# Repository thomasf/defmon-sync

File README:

defMon Sync Adapter is an adapter for the Commodore 64 computer. It is used to synchronize a tracker called defMon with other music equipment. It connects to the user port and outputs the following signals:
-LSDJ sync signal.
-nanoloop sync signal.
-midi clock.
-din sync.
-clock signal with adjustable resolution from 24ppqn to 2ppqn for Korg Volcas, TE Pocket Operators, Arturia Microbrute, MI Anushri etc.
It can only work as the master.
It should also work with Prophet64.

Original developer: Krzysztof Iwanowski

The firmware, PCB layouts and schematics are released under a Creative Commons cc-by-sa 3.0 license.

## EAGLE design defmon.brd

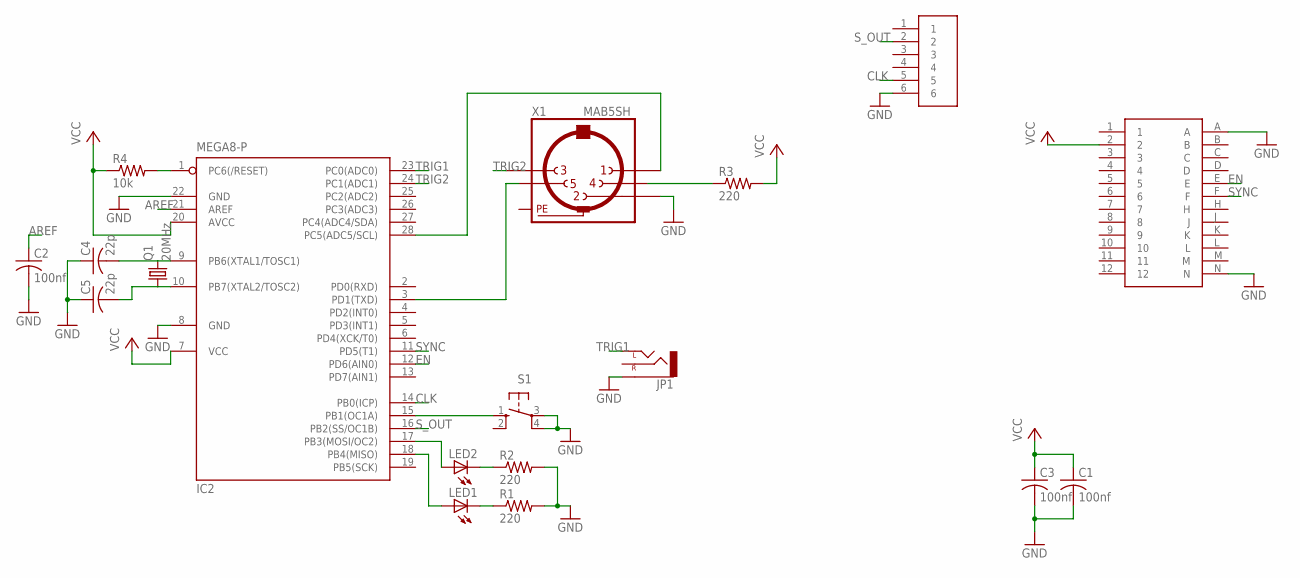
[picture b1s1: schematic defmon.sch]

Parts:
C1, C2, C3: 100nf; C025-025X050
C4, C5: 22p; C025-025X050
IC2: MEGA8-P; DIL28-3
JP1: AUDIO-JACKPTH; AUDIO-JACK
LED1, LED2: LED3MM
Q1: 20MHz; HC49U-V
R1, R2, R3: 220; 0204/7
R4: 10k; 0204/7
S1: 40-XX; B3F-40XX
U$1: GB
U$2: C64U
X1: MAB5SH

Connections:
AREF: C2.1, IC2.21 (AREF)
CLK: IC2.14 (PB0(ICP)), U$1.5
EN: IC2.12 (PD6(AIN0)), U$2.E
GND: C1.2, C2.2, C3.2, C4.1, C5.1, IC2.8 (GND), IC2.22 (GND), JP1.SLEEVE, R1.2, R2.2, S1.3, S1.4 (P1), U$1.6, U$2.A, U$2.N, X1.2
unnamed: LED2.K (C), R2.1
unnamed: LED1.K (C), R1.1
unnamed: R3.1, X1.4
unnamed: IC2.15 (PB1(OC1A)), S1.1 (S)
unnamed: IC2.17 (PB3(MOSI/OC2)), LED2.A
unnamed: IC2.18 (PB4(MISO)), LED1.A
unnamed: C4.2, IC2.9 (PB6(XTAL1/TOSC1)), Q1.2
unnamed: IC2.28 (PC5(ADC5/SCL)), X1.1
unnamed: C1.1, C3.1, IC2.7 (VCC), IC2.20 (AVCC), R3.2, R4.1, U$2.2
unnamed: C5.2, IC2.10 (PB7(XTAL2/TOSC2)), Q1.1
unnamed: IC2.1 (PC6(/RESET)), R4.2
unnamed: IC2.3 (PD1(TXD)), X1.5
PE: X1.PE, X1.PE@ (PE)
SYNC: IC2.11 (PD5(T1)), U$2.F
S_OUT: IC2.16 (PB2(SS/OC1B)), U$1.2
TRIG1: IC2.23 (PC0(ADC0)), JP1.TIP (LEFT)
TRIG2: IC2.24 (PC1(ADC1)), X1.3

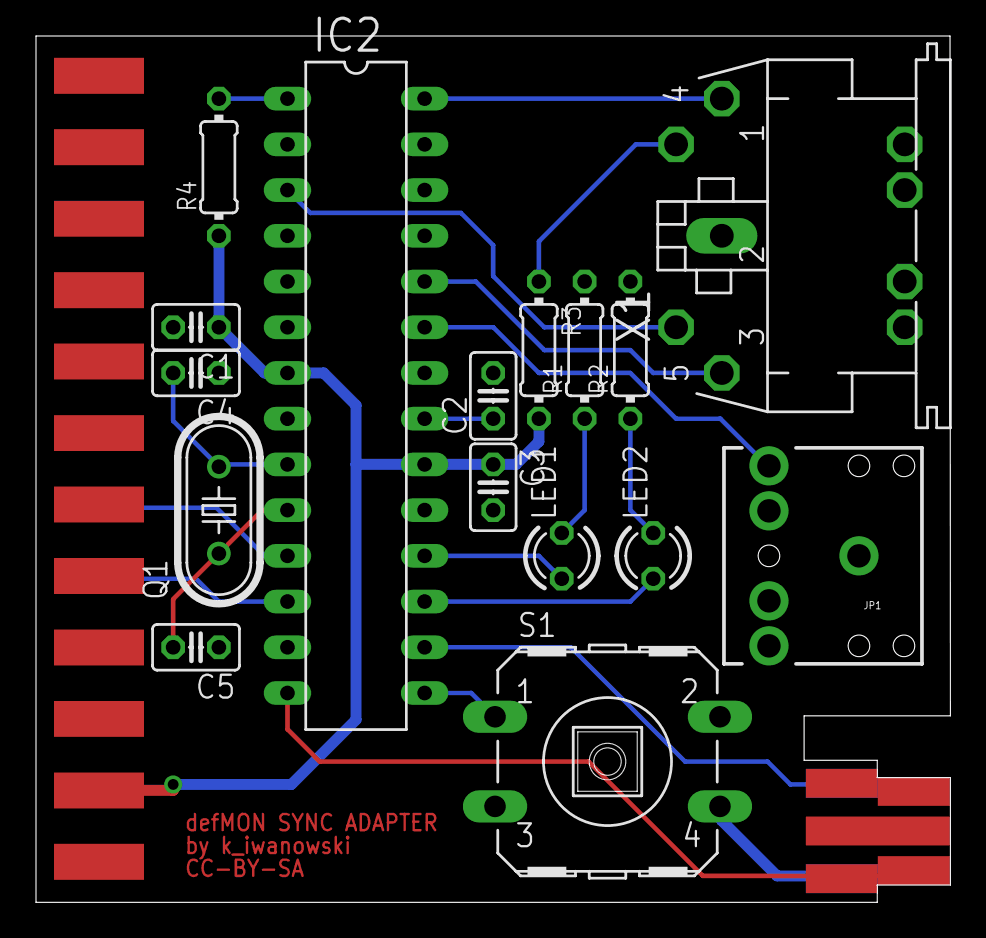
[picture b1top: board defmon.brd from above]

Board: 2 copper layers, 50.8 x 48.1 mm, 18 parts (0 on the bottom side), 21 nets.

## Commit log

2015-10-10 small fixes
2016-07-22 added a new jack socket

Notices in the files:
parts and their libraries:
SparkFun-Connectors: Licensing: Creative Commons ShareAlike 4.0 International - https://creativecommons.org/licenses/by-sa/4.0
